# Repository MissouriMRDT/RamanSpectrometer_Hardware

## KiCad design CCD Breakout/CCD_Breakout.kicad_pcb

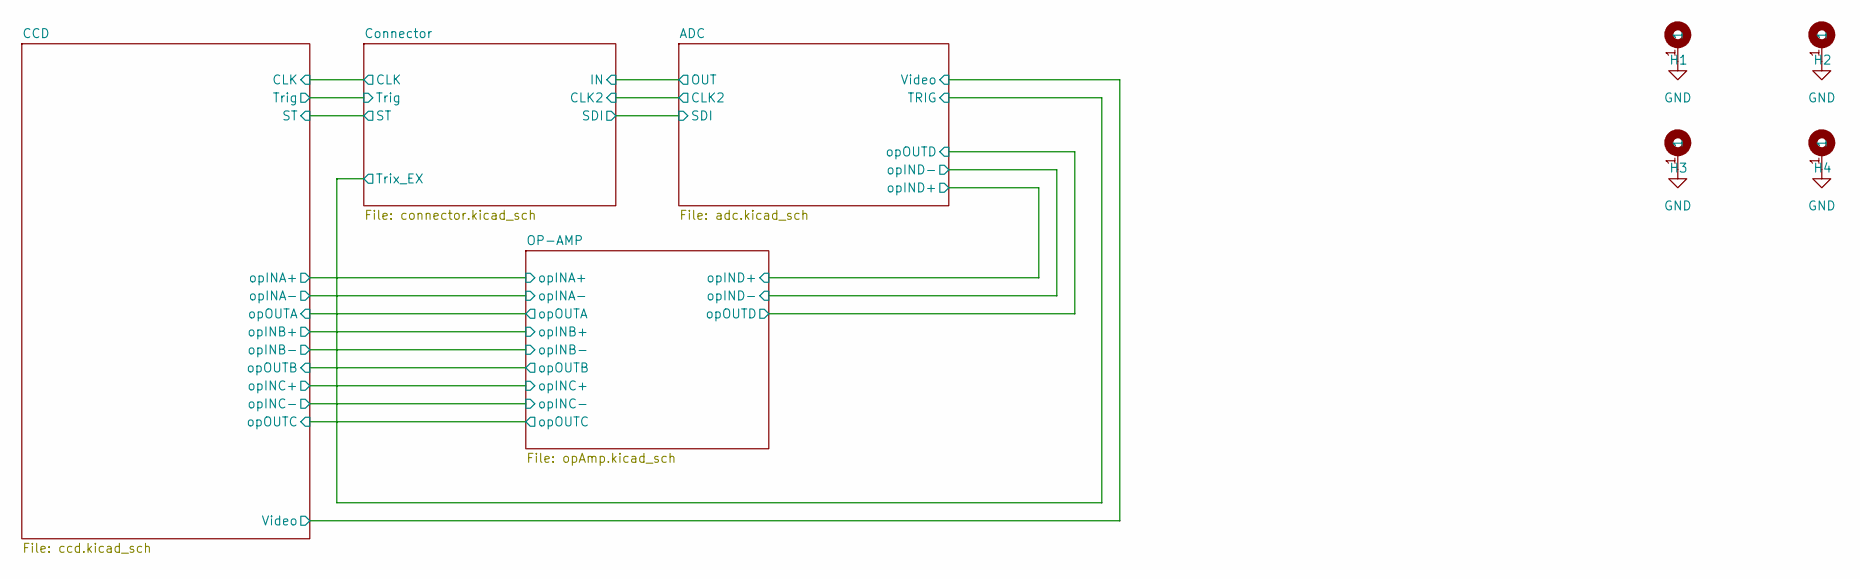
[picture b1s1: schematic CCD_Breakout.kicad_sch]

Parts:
H1, H2, H3, H4: 4_40_Hole_Pad_Via

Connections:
GND: H1.1, H2.1, H3.1, H4.1; also elsewhere on the board

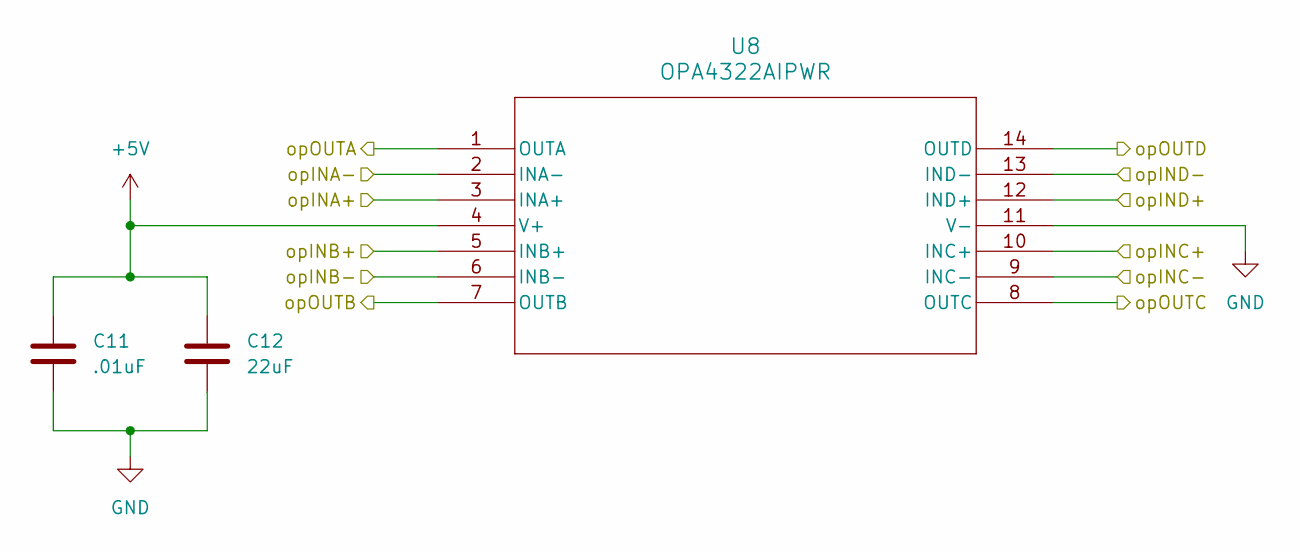
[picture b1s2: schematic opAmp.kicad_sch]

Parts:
C11: .01uF; C_0603_1608Metric_Pad1.08x0.95mm_HandSolder
C12: 22uF; C_0603_1608Metric_Pad1.08x0.95mm_HandSolder
U8: OPA4322AIPWR

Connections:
+1V: U8.5 (INB+); also elsewhere on the board
+1V8: U8.13 (IND-), U8.14 (OUTD); also elsewhere on the board
/ADC/Video: U8.8 (OUTC); also elsewhere on the board
/ADC/opIND+: U8.12 (IND+); also elsewhere on the board
/CCD/Videob: U8.10 (INC+); also elsewhere on the board
/CCD/opINA+: U8.3 (INA+); also elsewhere on the board
/CCD/opINA-: U8.1 (OUTA), U8.2 (INA-); also elsewhere on the board
/CCD/opINB-: U8.6 (INB-), U8.7 (OUTB); also elsewhere on the board
/CCD/opINC-: U8.9 (INC-); also elsewhere on the board
GND: C11.2, C12.2, U8.11 (V-); also elsewhere on the board

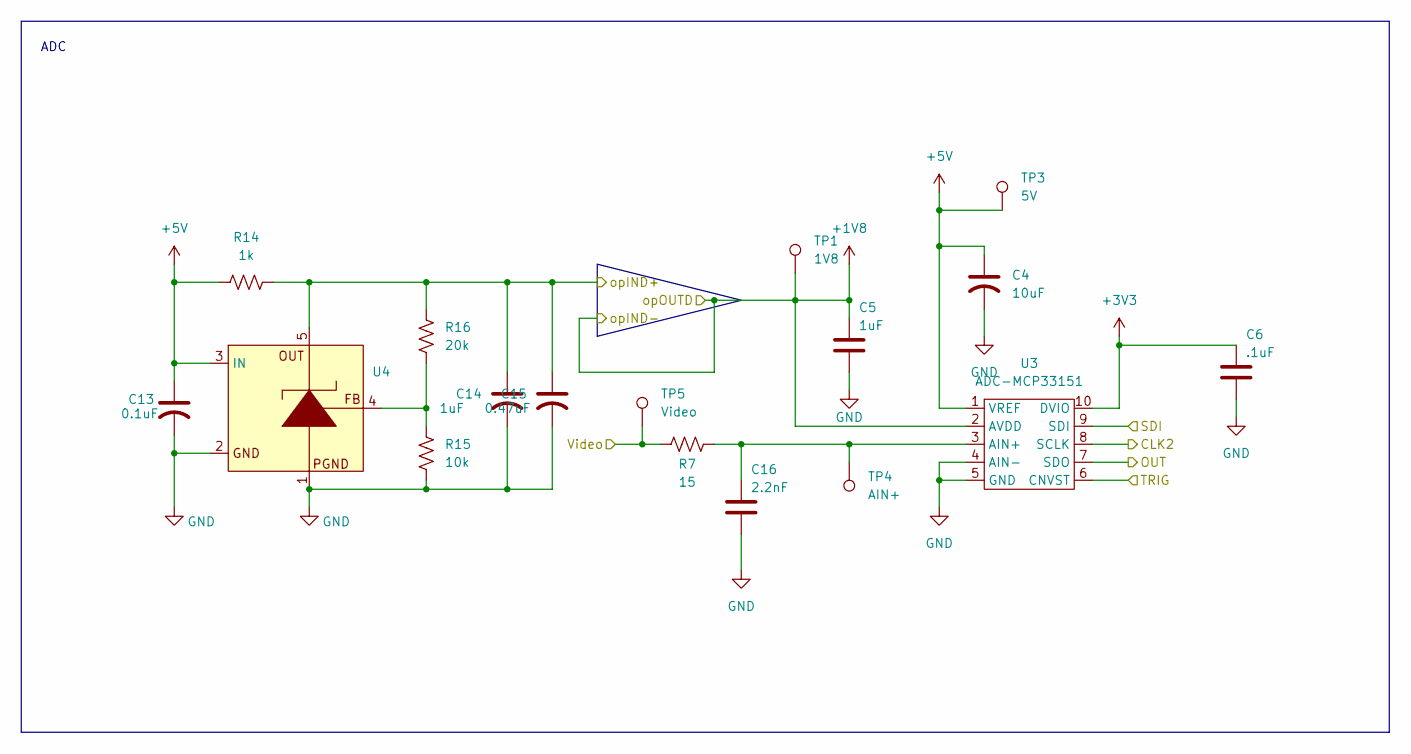
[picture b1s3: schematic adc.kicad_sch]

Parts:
C4: 10uF; CP_EIA-2012-12_Kemet-R_HandSolder
C5: 1uF; C_0603_1608Metric_Pad1.08x0.95mm_HandSolder
C6: .1uF; C_0603_1608Metric_Pad1.08x0.95mm_HandSolder
C13: 0.1uF; CP_EIA-2012-12_Kemet-R_HandSolder
C14: 1uF; CP_EIA-2012-12_Kemet-R_HandSolder
C15: 0.47uF; CP_EIA-2012-12_Kemet-R_HandSolder
C16: 2.2nF; C_0603_1608Metric_Pad1.08x0.95mm_HandSolder
R7: 15; R_0603_1608Metric_Pad0.98x0.95mm_HandSolder
R14: 1k; R_0603_1608Metric_Pad0.98x0.95mm_HandSolder
R15: 10k; R_0603_1608Metric_Pad0.98x0.95mm_HandSolder
R16: 20k; R_0603_1608Metric_Pad0.98x0.95mm_HandSolder
TP1: 1V8; TestPoint_Pad_D1.5mm
TP3: 5V; TestPoint_Pad_D1.5mm
TP4: AIN+; TestPoint_Pad_D1.5mm
TP5: Video; TestPoint_Pad_D1.5mm
U3: ADC-MCP33151; Untitled
U4: SOT-353_SC-70-5_Handsoldering

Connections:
+1V8: C5.1, TP1.1, U3.2 (AVDD); also elsewhere on the board
+3V3: C6.1, U3.10 (DVIO); also elsewhere on the board
/ADC/CLK2: U3.8 (SCLK); also elsewhere on the board
/ADC/OUT: U3.7 (SDO); also elsewhere on the board
/ADC/SDI: U3.9 (SDI); also elsewhere on the board
/ADC/TRIG: U3.6 (CNVST); also elsewhere on the board
/ADC/Video: R7.1, TP5.1; also elsewhere on the board
/ADC/opIND+: C14.1, C15.1, R14.2, R16.2, U4.5; also elsewhere on the board
GND: C4.2, C5.2, C6.2, C13.2, C14.2, C15.2, C16.2, R15.1, U3.4 (AIN-), U3.5 (GND), U4.1, U4.2; also elsewhere on the board
unnamed: R15.2, R16.1, U4.4
unnamed: C16.1, R7.2, TP4.1, U3.3 (AIN+)

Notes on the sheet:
ADC

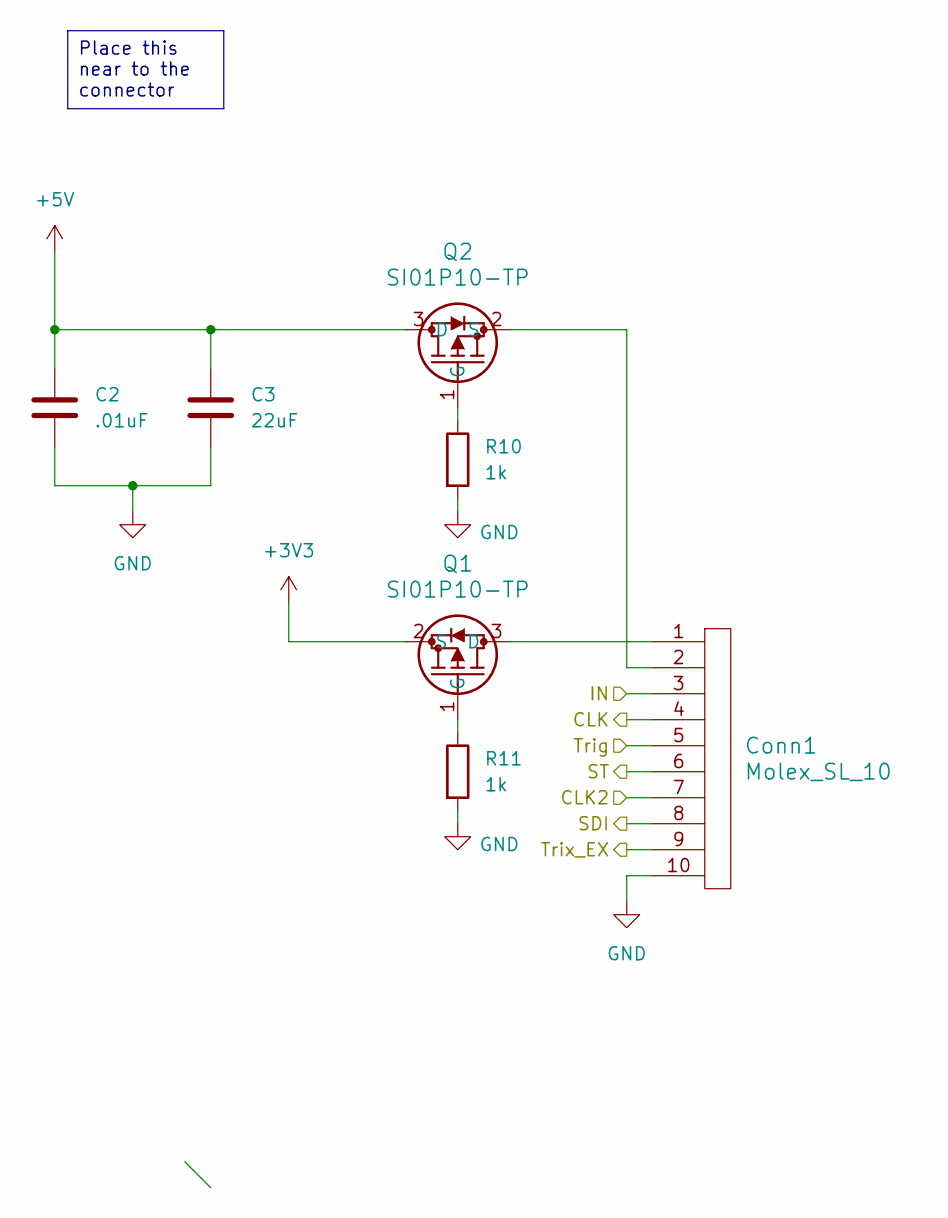
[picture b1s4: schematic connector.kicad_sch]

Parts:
C2: .01uF; C_0603_1608Metric_Pad1.08x0.95mm_HandSolder
C3: 22uF; C_0603_1608Metric_Pad1.08x0.95mm_HandSolder
Conn1: Molex_SL_10; MOLEX_SL_10_Vertical
Q1, Q2: SI01P10-TP; SOT-23_MCC-L
R10, R11: 1k; R_0603_1608Metric_Pad0.98x0.95mm_HandSolder

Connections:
+3V3: Q1.2 (S); also elsewhere on the board
/ADC/CLK2: Conn1.7; also elsewhere on the board
/ADC/OUT: Conn1.3; also elsewhere on the board
/ADC/SDI: Conn1.8; also elsewhere on the board
/ADC/TRIG: Conn1.9; also elsewhere on the board
/CCD/CLK: Conn1.4; also elsewhere on the board
/CCD/ST: Conn1.6; also elsewhere on the board
/CCD/Trig: Conn1.5; also elsewhere on the board
GND: C2.2, C3.2, Conn1.10, R10.2, R11.2; also elsewhere on the board
unnamed: Conn1.1, Q1.3 (D)
unnamed: Q1.1 (G), R11.1
unnamed: Q2.1 (G), R10.1

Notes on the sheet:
Place this near to the connector

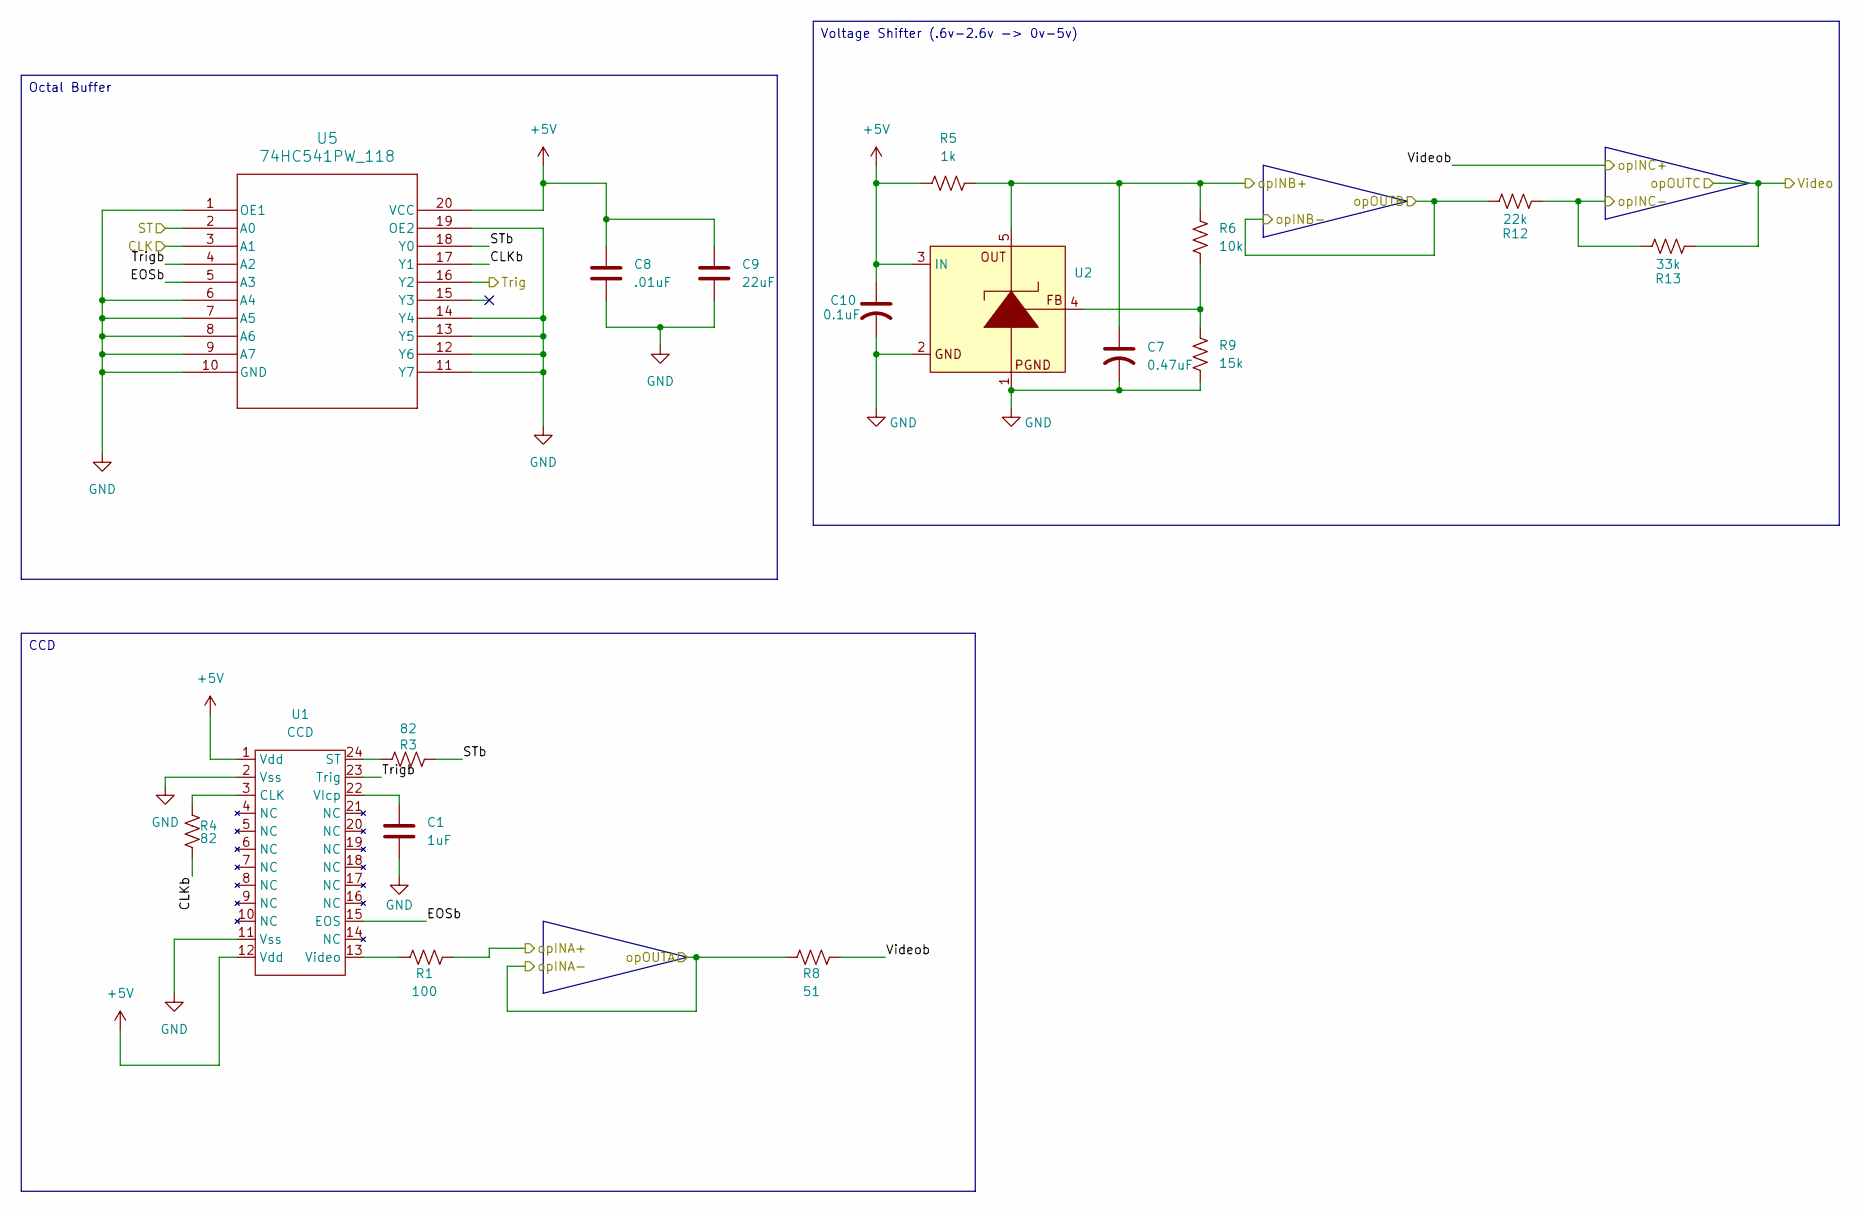
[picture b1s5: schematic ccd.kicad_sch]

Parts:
C1: 1uF; C_0603_1608Metric_Pad1.08x0.95mm_HandSolder
C7: 0.47uF; CP_EIA-2012-12_Kemet-R_HandSolder
C8: .01uF; C_0603_1608Metric_Pad1.08x0.95mm_HandSolder
C9: 22uF; C_0603_1608Metric_Pad1.08x0.95mm_HandSolder
C10: 0.1uF; CP_EIA-2012-12_Kemet-R_HandSolder
R1: 100; R_0603_1608Metric_Pad0.98x0.95mm_HandSolder
R3, R4: 82; R_0603_1608Metric_Pad0.98x0.95mm_HandSolder
R5: 1k; R_0603_1608Metric_Pad0.98x0.95mm_HandSolder
R6: 10k; R_0603_1608Metric_Pad0.98x0.95mm_HandSolder
R8: 51; R_0603_1608Metric_Pad0.98x0.95mm_HandSolder
R9: 15k; R_0603_1608Metric_Pad0.98x0.95mm_HandSolder
R12: 22k; R_0603_1608Metric_Pad0.98x0.95mm_HandSolder
R13: 33k; R_0603_1608Metric_Pad0.98x0.95mm_HandSolder
U1: CCD; ED90055-ND
U2: SOT-353_SC-70-5_Handsoldering
U5: 74HC541PW_118

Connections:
+1V: C7.1, R5.2, R6.2, U2.5; also elsewhere on the board
/ADC/Video: R13.2; also elsewhere on the board
/CCD/CLK: U5.3 (A1); also elsewhere on the board
/CCD/CLKb: R4.2, U5.17 (Y1)
/CCD/EOSb: U1.15 (EOS), U5.5 (A3)
/CCD/ST: U5.2 (A0); also elsewhere on the board
/CCD/STb: R3.1, U5.18 (Y0)
/CCD/Trig: U5.16 (Y2); also elsewhere on the board
/CCD/Trigb: U1.23 (Trig), U5.4 (A2)
/CCD/Videob: R8.1; also elsewhere on the board
/CCD/opINA+: R1.1; also elsewhere on the board
/CCD/opINA-: R8.2; also elsewhere on the board
/CCD/opINB-: R12.1; also elsewhere on the board
/CCD/opINC-: R12.2, R13.1; also elsewhere on the board
GND: C1.2, C7.2, C8.2, C9.2, C10.2, R9.1, U1.2 (Vss), U1.11 (Vss), U2.1, U2.2, U5.1 (OE1), U5.6 (A4), U5.7 (A5), U5.8 (A6), U5.9 (A7), U5.10 (GND), U5.11 (Y7), U5.12 (Y6), U5.13 (Y5), U5.14 (Y4), U5.19 (OE2); also elsewhere on the board
unnamed: R6.1, R9.2, U2.4
unnamed: R4.1, U1.3 (CLK)
unnamed: R3.2, U1.24 (ST)
unnamed: C1.1, U1.22 (VIcp)
unnamed: R1.2, U1.13 (Video)

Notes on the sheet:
CCD
Octal Buffer
Voltage Shifter (.6v-2.6v -> 0v-5v)

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
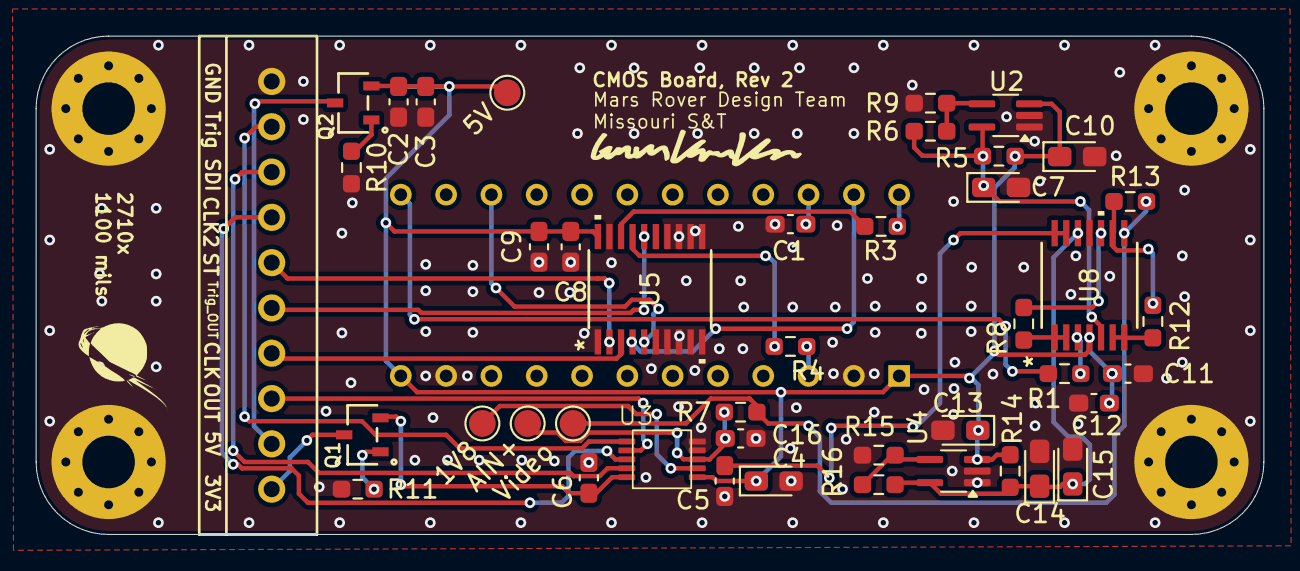
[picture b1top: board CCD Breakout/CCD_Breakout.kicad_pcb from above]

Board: 2 copper layers, 68.8 x 27.9 mm, 48 parts (1 on the bottom side), 34 nets.

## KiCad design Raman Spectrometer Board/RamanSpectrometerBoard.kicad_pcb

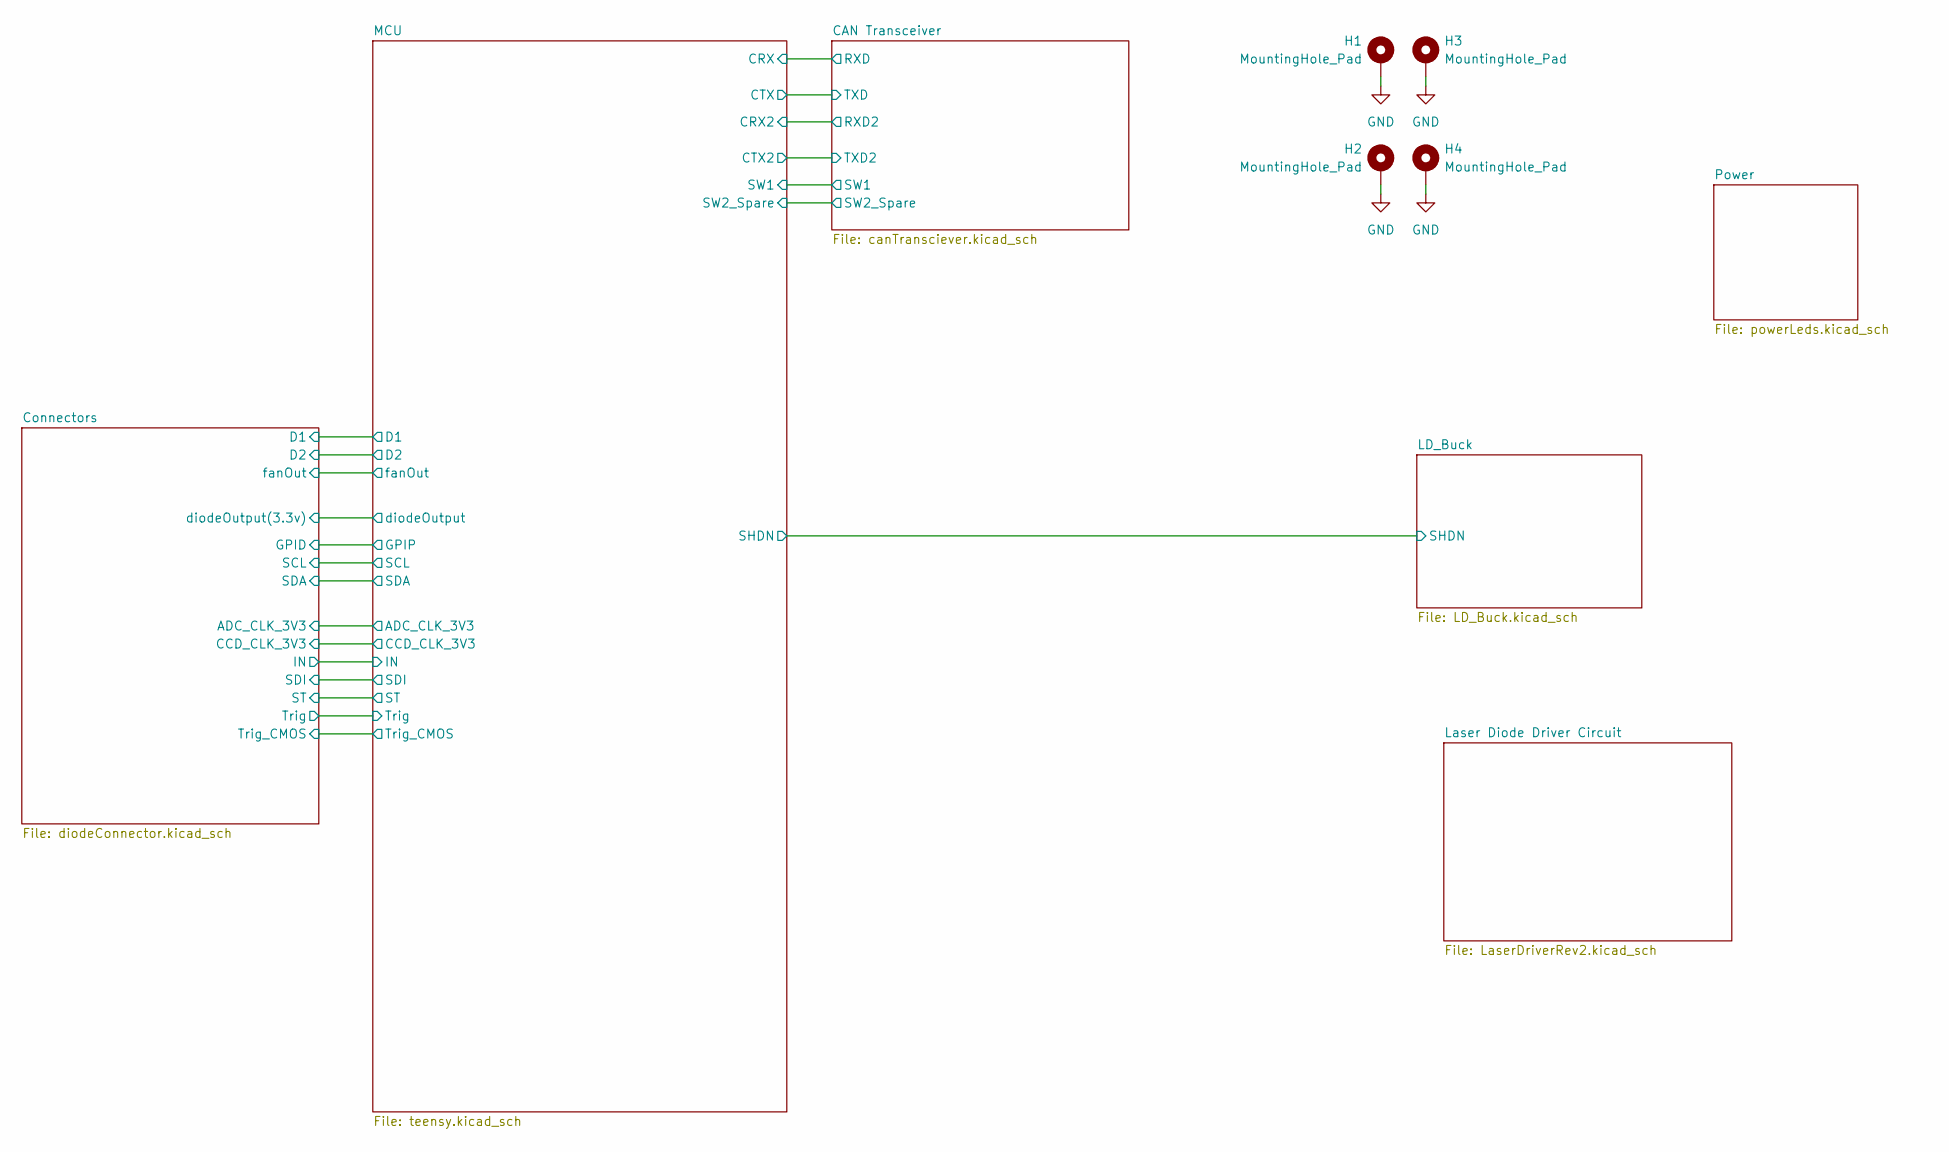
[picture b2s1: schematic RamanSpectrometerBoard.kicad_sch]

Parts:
H1, H2, H3, H4: MountingHole_Pad; MountingHole_3mm_Pad_Via

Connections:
GND: H1.1, H2.1, H3.1, H4.1; also elsewhere on the board

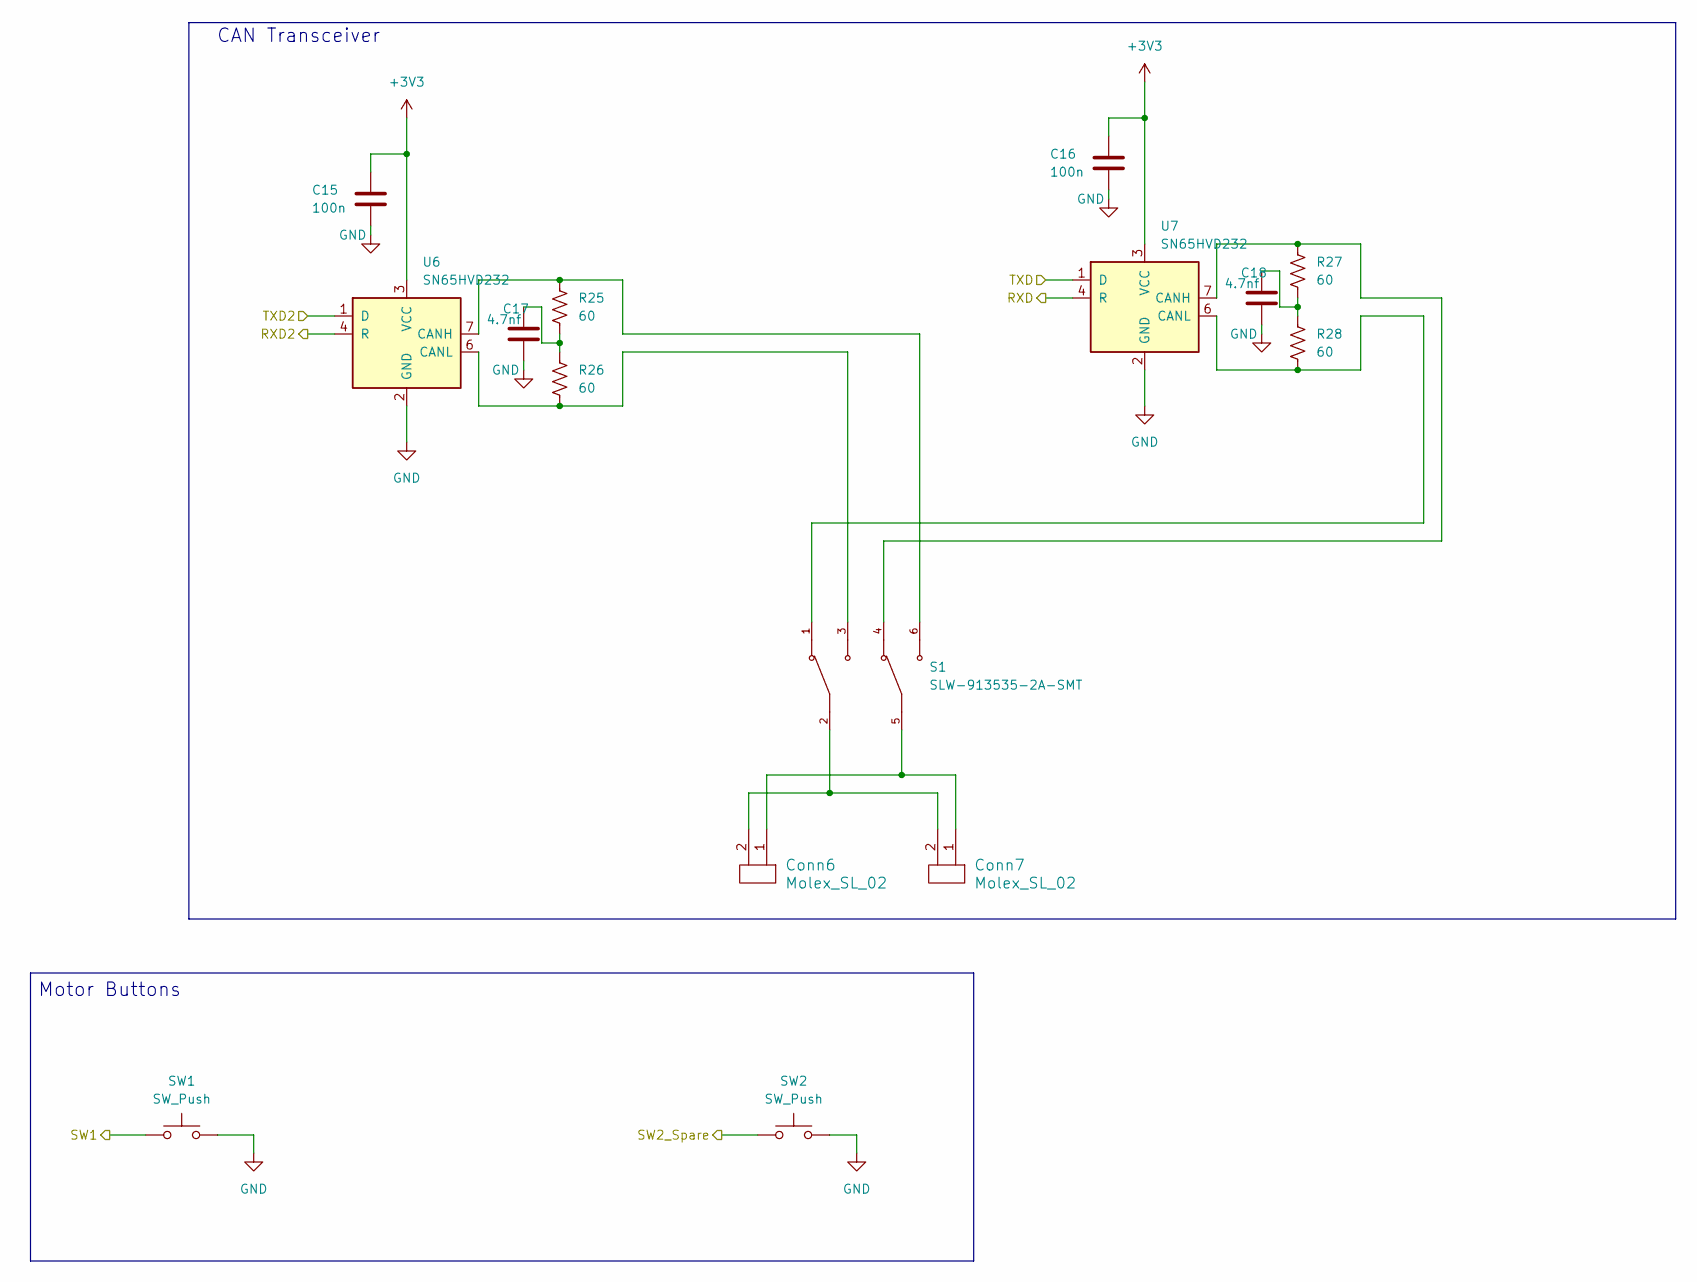
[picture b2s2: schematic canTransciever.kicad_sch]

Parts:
C15, C16: 100n; C_0603_1608Metric_Pad1.08x0.95mm_HandSolder
C17, C18: 4.7nf; C_0603_1608Metric_Pad1.08x0.95mm_HandSolder
Conn6, Conn7: Molex_SL_02; MOLEX_SL_02_Vertical
R25, R26, R27, R28: 60; R_0603_1608Metric_Pad0.98x0.95mm_HandSolder
S1: SLW-913535-2A-SMT; SW_SLW-913535-2A-SMT; PARTREV 1.01
SW1, SW2: SW_Push; SW_SPST_TL3305A
U6, U7: SN65HVD232; SOIC-8_3.9x4.9mm_P1.27mm

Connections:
+3V3: C15.1, C16.1, U6.3 (VCC), U7.3 (VCC); also elsewhere on the board
/CAN Transceiver/RXD: U7.4 (R); also elsewhere on the board
/CAN Transceiver/RXD2: U6.4 (R); also elsewhere on the board
/CAN Transceiver/SW1: SW1.1; also elsewhere on the board
/CAN Transceiver/SW2_Spare: SW2.1; also elsewhere on the board
/CAN Transceiver/TXD: U7.1 (D); also elsewhere on the board
/CAN Transceiver/TXD2: U6.1 (D); also elsewhere on the board
GND: C15.2, C16.2, C17.2, C18.2, SW1.2, SW2.2, U6.2 (GND), U7.2 (GND); also elsewhere on the board
unnamed: C17.1, R25.2, R26.1
unnamed: C18.1, R27.2, R28.1
unnamed: Conn6.1, Conn7.1, S1.5
unnamed: Conn6.2, Conn7.2, S1.2
unnamed: R25.1, S1.6, U6.7 (CANH)
unnamed: R26.2, S1.3, U6.6 (CANL)
unnamed: R27.1, S1.4, U7.7 (CANH)
unnamed: R28.2, S1.1, U7.6 (CANL)

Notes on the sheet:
CAN Transceiver
Motor Buttons

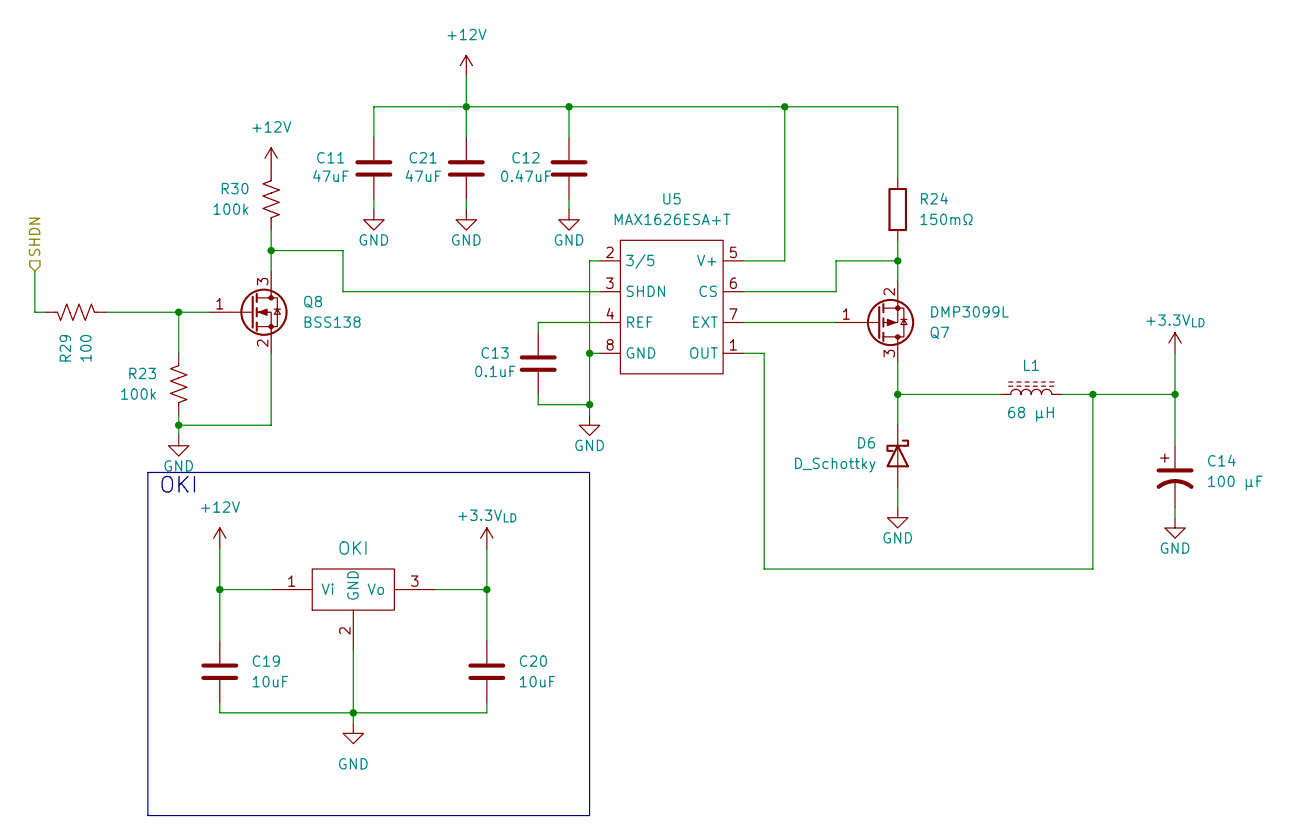
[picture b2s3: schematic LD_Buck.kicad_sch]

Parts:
C11, C21: 47uF; C_0603_1608Metric
C12: 0.47uF; C_0603_1608Metric
C13: 0.1uF; C_0603_1608Metric
C14: 100 µF; CAPMP6.3X3.2_2.8N_KEM
C19, C20: 10uF; C_0603_1608Metric_Pad1.08x0.95mm_HandSolder
D6: D_Schottky; SODFL3617X108N
L1: 68 µH; L_Bourns_SRP7028A_7.3x6.6mm
Q7: DMP3099L; SOT-23
Q8: BSS138; SOT-23
R23, R30: 100k; R_0603_1608Metric
R24: 150mΩ; R_1206_3216Metric_Pad1.30x1.75mm_HandSolder; Part No. WFC1206R1500FE66
R29: 100; R_0603_1608Metric
U5: MAX1626ESA+T; 21-0041B_8_MXM
U8: OKI; Converter_DCDC_Murata_OKI-78SR_Vertical

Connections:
+3.3V_{LD}: C14.1, C20.1, L1.2, U5.1 (OUT), U8.3 (Vo); also elsewhere on the board
+12V: C11.1, C12.1, C19.1, C21.1, R24.1, R30.1, U5.5 (V+), U8.1 (Vi); also elsewhere on the board
/LD_Buck/SHDN: R29.1; also elsewhere on the board
GND: C11.2, C12.2, C13.2, C14.2, C19.2, C20.2, C21.2, D6.2 (A), Q8.2 (S), R23.2, U5.2 (3/5), U5.8 (GND), U8.2 (GND); also elsewhere on the board
unnamed: D6.1 (K), L1.1, Q7.3 (D)
unnamed: Q7.1 (G), U5.7 (EXT)
unnamed: Q7.2 (S), R24.2, U5.6 (CS)
unnamed: Q8.3 (D), R30.2, U5.3 (SHDN)
unnamed: Q8.1 (G), R23.1, R29.2
unnamed: C13.1, U5.4 (REF)

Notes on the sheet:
OKI

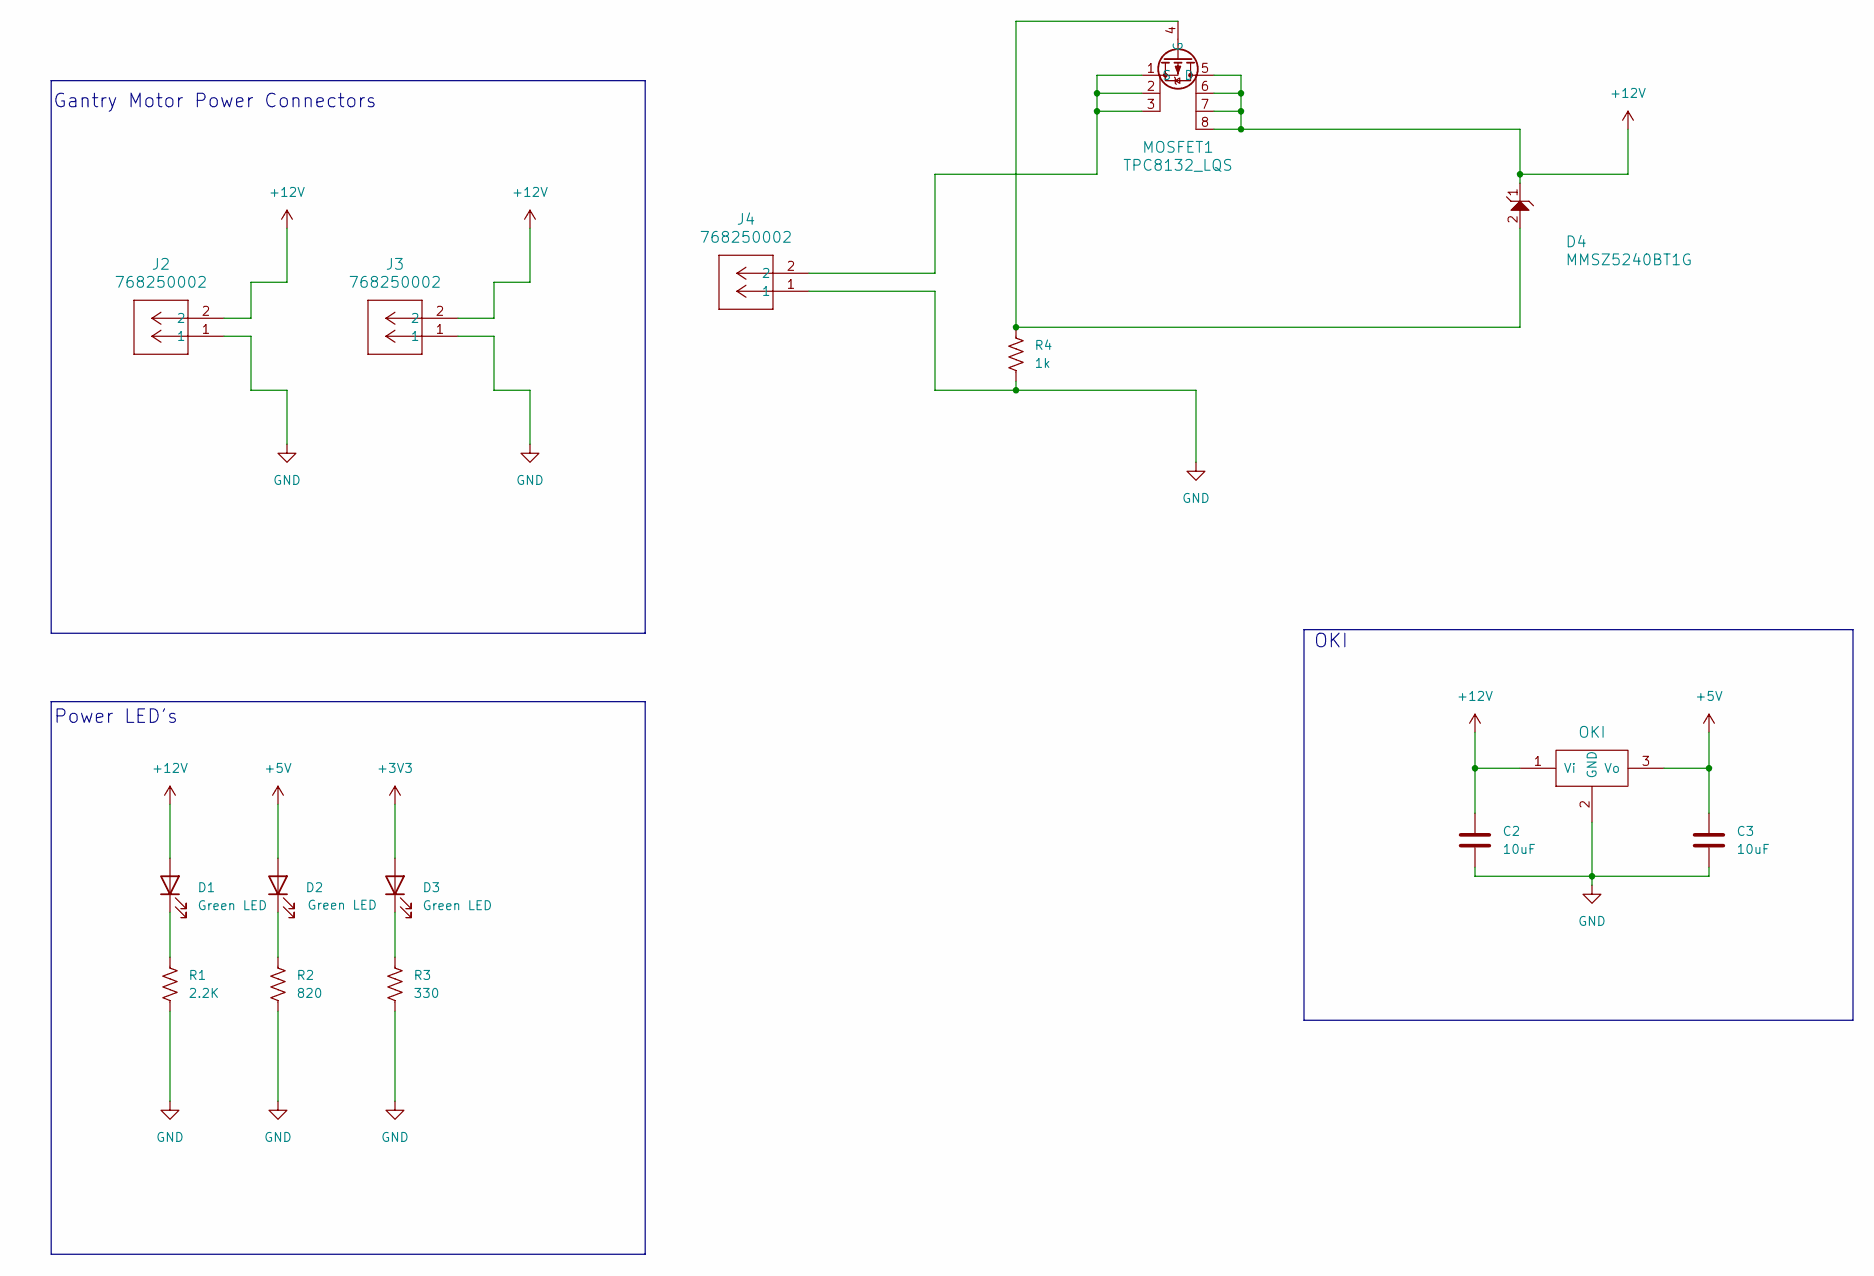
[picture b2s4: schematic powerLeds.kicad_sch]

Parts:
C2, C3: 10uF; C_0603_1608Metric_Pad1.08x0.95mm_HandSolder
D1, D2, D3: Green LED; LED_0603_1608Metric_Pad1.05x0.95mm_HandSolder
D4: MMSZ5240BT1G; SOD-123_ONS-L
J2, J3, J4: 768250002; CONN_SD-76825-0100_02_MOL
MOSFET1: TPC8132_LQS; SOIC-8_3.9x4.9mm_P1.27mm
R1: 2.2K; R_0603_1608Metric_Pad0.98x0.95mm_HandSolder
R2: 820; R_0603_1608Metric_Pad0.98x0.95mm_HandSolder
R3: 330; R_0603_1608Metric_Pad0.98x0.95mm_HandSolder
R4: 1k; R_0603_1608Metric_Pad0.98x0.95mm_HandSolder
U2: OKI; OKI_Horizontal

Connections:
+3V3: D3.2 (A); also elsewhere on the board
+5V: C3.1, D2.2 (A), U2.3 (Vo); also elsewhere on the board
+12V: C2.1, D1.2 (A), D4.1, J2.2, J3.2, MOSFET1.5 (D), MOSFET1.6, MOSFET1.7, MOSFET1.8, U2.1 (Vi); also elsewhere on the board
GND: C2.2, C3.2, J2.1, J3.1, J4.1, R1.2, R2.2, R3.2, R4.2, U2.2 (GND); also elsewhere on the board
unnamed: D1.1 (K), R1.1
unnamed: D2.1 (K), R2.1
unnamed: D3.1 (K), R3.1
unnamed: D4.2, MOSFET1.4 (G), R4.1
unnamed: J4.2, MOSFET1.1 (S), MOSFET1.2, MOSFET1.3

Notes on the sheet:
OKI
Gantry Motor Power Connectors
Power LED's

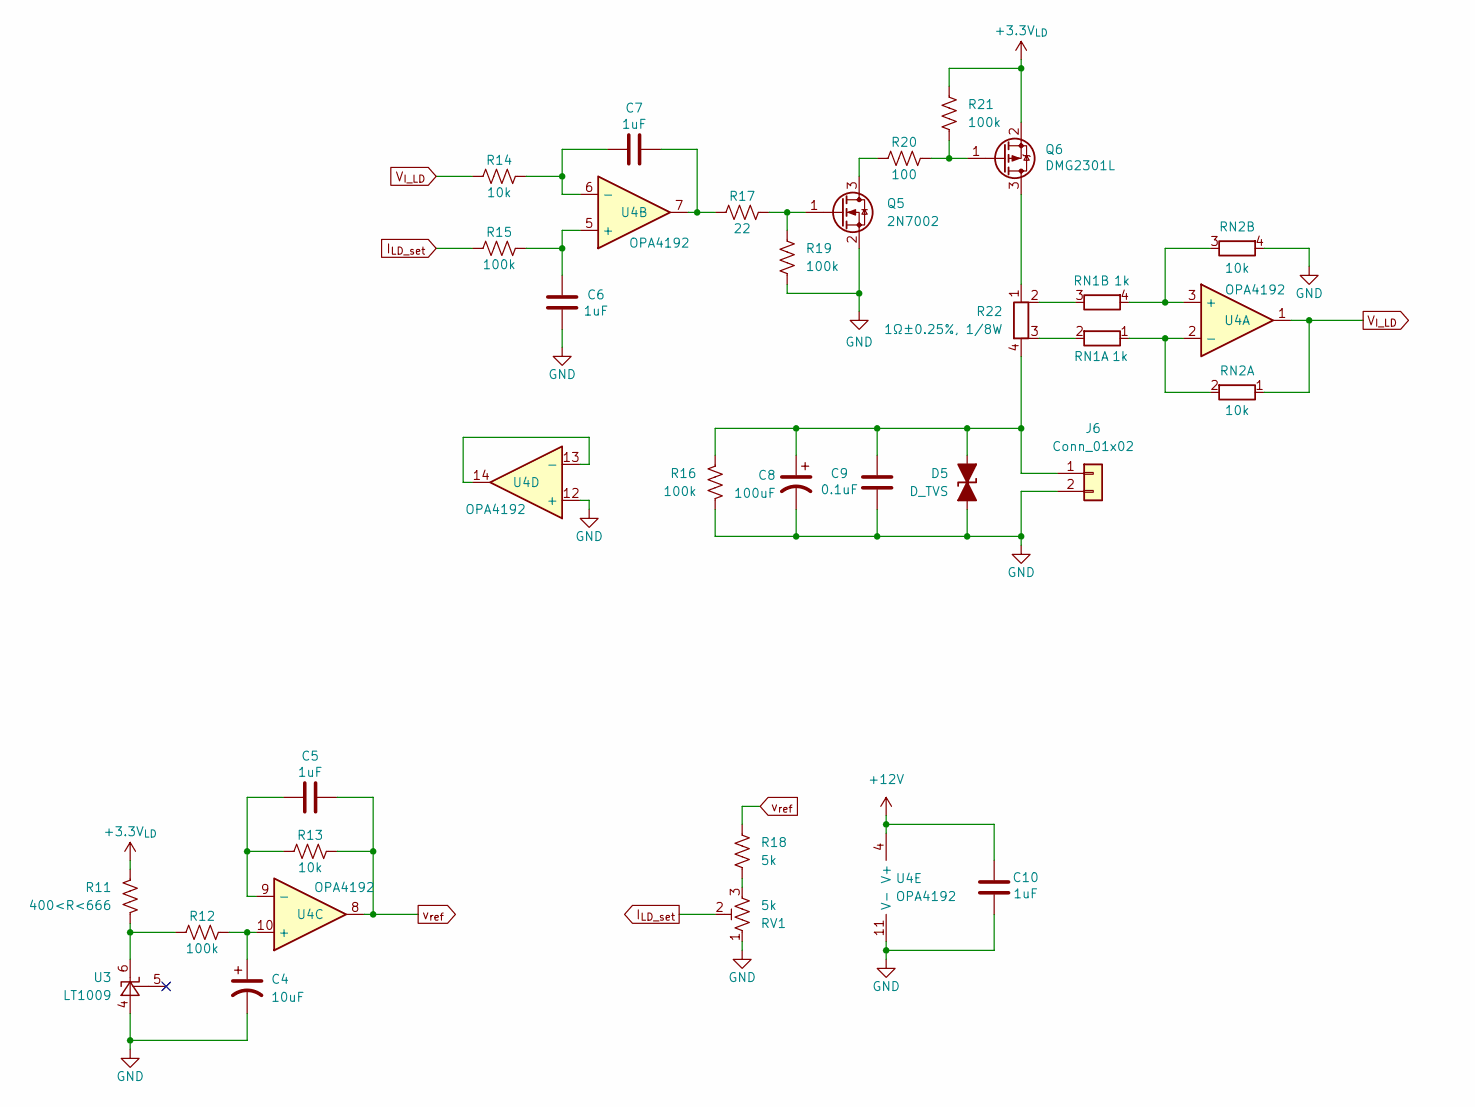
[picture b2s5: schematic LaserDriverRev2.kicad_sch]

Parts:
C4: 10uF; CP_Elec_5x5.8
C5, C6, C7, C10: 1uF; C_0603_1608Metric
C8: 100uF; CP_Elec_6.3x5.8
C9: 0.1uF; C_0603_1608Metric
D5: D_TVS; D_0603_1608Metric
J6: Conn_01x02; JST_EH_S2B-EH_1x02_P2.50mm_Horizontal
Q5: 2N7002; SOT-23
Q6: DMG2301L; SOT-23
R11: 400<R<666; R_0603_1608Metric
R12, R15, R16, R19, R21: 100k; R_0603_1608Metric
R13, R14: 10k; R_0603_1608Metric
R17: 22; R_0603_1608Metric
R18: 5k; R_0603_1608Metric
R20: 100; R_0603_1608Metric
R22: 1Ω±0.25%, 1/8W; R_Shunt_0805_2012Metric
RN1: 1k; R_Array_Convex_2x0606
RN2: 10k; R_Array_Convex_2x0606
RV1: 5k; Potentiometer_Bourns_3296Y_Vertical
U3: LT1009; SOIC-8_3.9x4.9mm_P1.27mm
U4: OPA4192; SOIC-14_3.9x8.7mm_P1.27mm

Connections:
+3.3V_{LD}: Q6.2 (S), R11.1, R21.1; also elsewhere on the board
+12V: C10.1, U4.4 (V+); also elsewhere on the board
GND: C4.2, C6.1, C8.2, C9.2, C10.2, D5.1 (A1), J6.2, Q5.2 (S), R16.2, R19.2, RN2.4 (R2.2), RV1.1, U3.4 (A), U4.11 (V-), U4.12 (+); also elsewhere on the board
I_{LD_set}: R15.1, RV1.2
unnamed: C7.2, R17.1, U4.7
unnamed: C8.1, C9.1, D5.2 (A2), J6.1, R16.1, R22.4
unnamed: Q5.3 (D), R20.1
unnamed: Q5.1 (G), R17.2, R19.1
unnamed: Q6.3 (D), R22.1
unnamed: Q6.1 (G), R20.2, R21.2
unnamed: R11.2, R12.1, U3.6 (K), U3.8 (K)
unnamed: R18.2, RV1.3
unnamed: RN1.1 (R1.1), RN2.2 (R1.2), U4.2 (-)
unnamed: R22.3, RN1.2 (R1.2)
unnamed: R22.2, RN1.3 (R2.1)
unnamed: RN1.4 (R2.2), RN2.3 (R2.1), U4.3 (+)
unnamed: C6.2, R15.2, U4.5 (+)
unnamed: C7.1, R14.2, U4.6 (-)
unnamed: C4.1, R12.2, U4.10 (+)
unnamed: C5.1, R13.1, U4.9 (-)
unnamed: U4.13 (-), U4.14
V_{I_LD}: R14.1, RN2.1 (R1.1), U4.1
v_{ref}: C5.2, R13.2, R18.1, U4.8
